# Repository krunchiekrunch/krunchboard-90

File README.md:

# krunchboard-90
A custom 75% (84+5+1) ANSI mechanical keyboard powered by a Raspberry Pi Pico with KMK

# About
This keyboard has 84 regular keys, 5 programmable macro keys, and 1 switch within the rotary encoder.

## Special Keys

Media Controls:

- Double tap F1: Previous media

- Double tap F2: Pause media

- Double tap F3: Next media

Rotary encoder:

- Turn: Volume Up/Down

- Press/Fn and turn: Brightness Up/Down

- Double press: Mute

[KLE](https://www.keyboard-layout-editor.com/##@@_a:6%3B&=Esc&_a:4%3B&=F1%0AMute&=F2%0AVOLD&=F3%0AVOLU&=F4%0APrev&=F5%0APause&=F6%0ANext&_a:6%3B&=F7&=F8&=F9&=F10&_a:4%3B&=F11%0ABRID&=F12%0ABRIU&_a:5%3B&=PrtSc%0ANmLk&=Pause%0AScrLk&=Delete%0AInsert&_a:4%3B&=Rotary%0AMute%3B&@=~%0A%60&=!%0A1&=%2F@%0A2&=%23%0A3&=$%0A4&=%25%0A5&=%5E%0A6&=%2F&%0A7&=*%0A8&=(%0A9&=)%0A0&=%2F_%0A-&=+%0A%2F=&_a:6&w:2%3B&=Backspace&=Home&_a:7%3B&=%3B&@_a:4&w:1.5%3B&=Tab&=Q&=W&=E&=R&=T&=Y&=U&=I&=O&=P&=%7B%0A%5B&=%7D%0A%5D&_w:1.5%3B&=%7C%0A%5C&_a:6%3B&=Page%20Up&_a:7%3B&=%3B&@_a:4&w:1.75%3B&=Caps%20Lock&=A&=S&=D&=F&=G&=H&=J&=K&=L&=%2F:%0A%2F%3B&=%22%0A'&_a:6&w:2.25%3B&=Enter&=Page%20Down&_a:7%3B&=%3B&@_a:6&w:2.25%3B&=Shift&_a:4%3B&=Z&=X&=C&=V&=B&=N&=M&=%3C%0A,&=%3E%0A.&=%3F%0A%2F%2F&_a:6&w:1.75%3B&=Shift&_a:7%3B&=%E2%86%91&_a:6%3B&=End&_a:7%3B&=%3B&@_a:6&w:1.25%3B&=Ctrl&_w:1.25%3B&=Win&_w:1.25%3B&=Alt&_a:7&w:6.25%3B&=&_a:6%3B&=Alt&=Fn&=Ctrl&_a:7%3B&=%E2%86%90&=%E2%86%93&=%E2%86%92&=)

# Images

| PCB                      | 3D View                         |
|--------------------------|---------------------------------|
|    |  |
|  |    | 

# BOM

| Qty | Item                                         | Notes                                     | Cost (USD)       | URL |
|-----|----------------------------------------------|-------------------------------------------|------------------|-----|
| 89  | MX-Style key switches                        | Already have                              | 9.90             | [AE](https://www.aliexpress.com/item/1005002378701948.html) |
| 89  | Kailh MX hotswap socket                      | Already have                              | 8.11             | [AE](https://www.aliexpress.com/item/1005007052649640.html) |
| 90  | 1N4148W SOD-123 Diode                        | Already have                              | 2.32             | [AE](https://www.aliexpress.com/item/1005009063199018.html) |
| 1   | EC11E Rotary encoder (With switch)           | Already have                              | 2.42             | [AE](https://www.aliexpress.com/item/1005008413622715.html) |
| 3   | MX Stabilizer (3x2u, 1x6.25u)                | Already have                              | 2.42             | [AE](https://www.aliexpress.com/item/1005007212869086.html) |
| 1   | ANSI Keycaps set                             | Already have                              | 7.00             | [AE](https://www.aliexpress.com/item/1005007321700850.html) |
| 1   | Raspbery Pi Pico (RP2040 or RP2350)          | Already have                              | 2.30             | [AE](https://www.aliexpress.com/item/1005006054409042.html) |
| 1   | USB-C Socket (SMD)                           | Already have                              | 1.00             | N/A |
| 2   | 5.1k/4.7k 0805 SMD resistor                  | Already have                              | 1.00             | N/A |
| 4   | M2 Screw (13.9mm max, I used 12mm)           | Already have                              | 1.42             | [AE](https://www.aliexpress.com/item/1005003670389142.html) |
| 4   | M2 Heatset Insert (OD3.2mm, 3mm deep)        | Already have                              | 1.73             | [AE](https://www.aliexpress.com/item/1005007640664497.html) |
| 6   | Stick-on rubber feet (Optional)              | Already have                              | 1.18             | [AE](https://www.aliexpress.com/item/1005006832476105.html) |
| 1   | PCB                                          | (Shipping/Tax included + $20 coupon)      | 15.58            | [JLCPCB](https://jlcpcb.com) |
| 1   | 3D Printed case and plate (Blueprint only)   | print-legion                              | 4.65             | N/A |
|     |                                              | Total:                                    | 56.38 [20.23]    |     |

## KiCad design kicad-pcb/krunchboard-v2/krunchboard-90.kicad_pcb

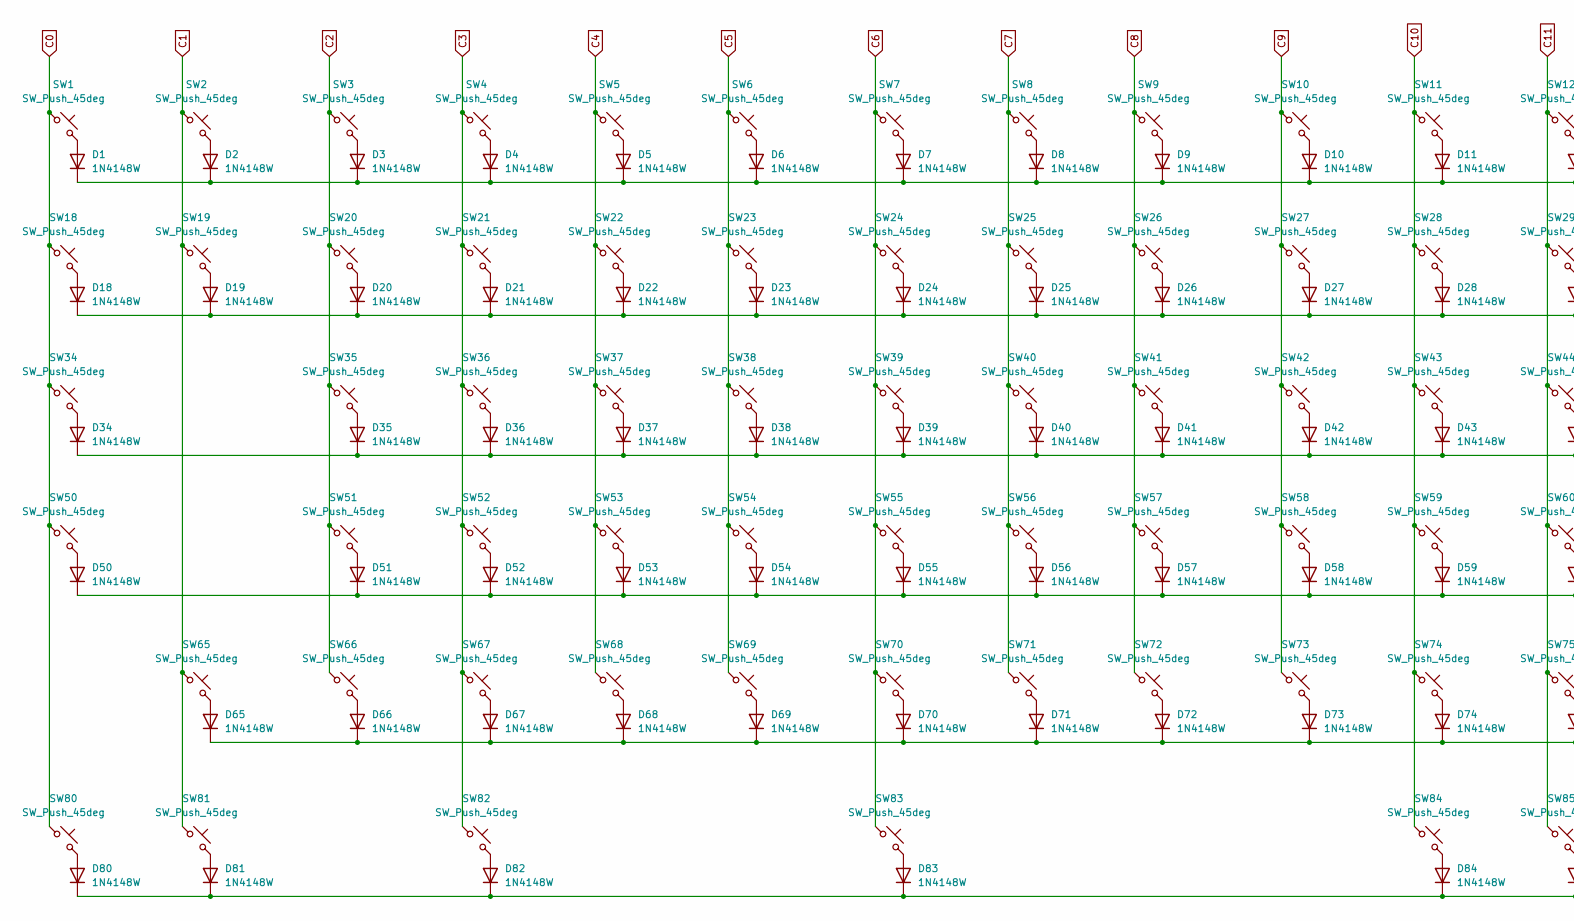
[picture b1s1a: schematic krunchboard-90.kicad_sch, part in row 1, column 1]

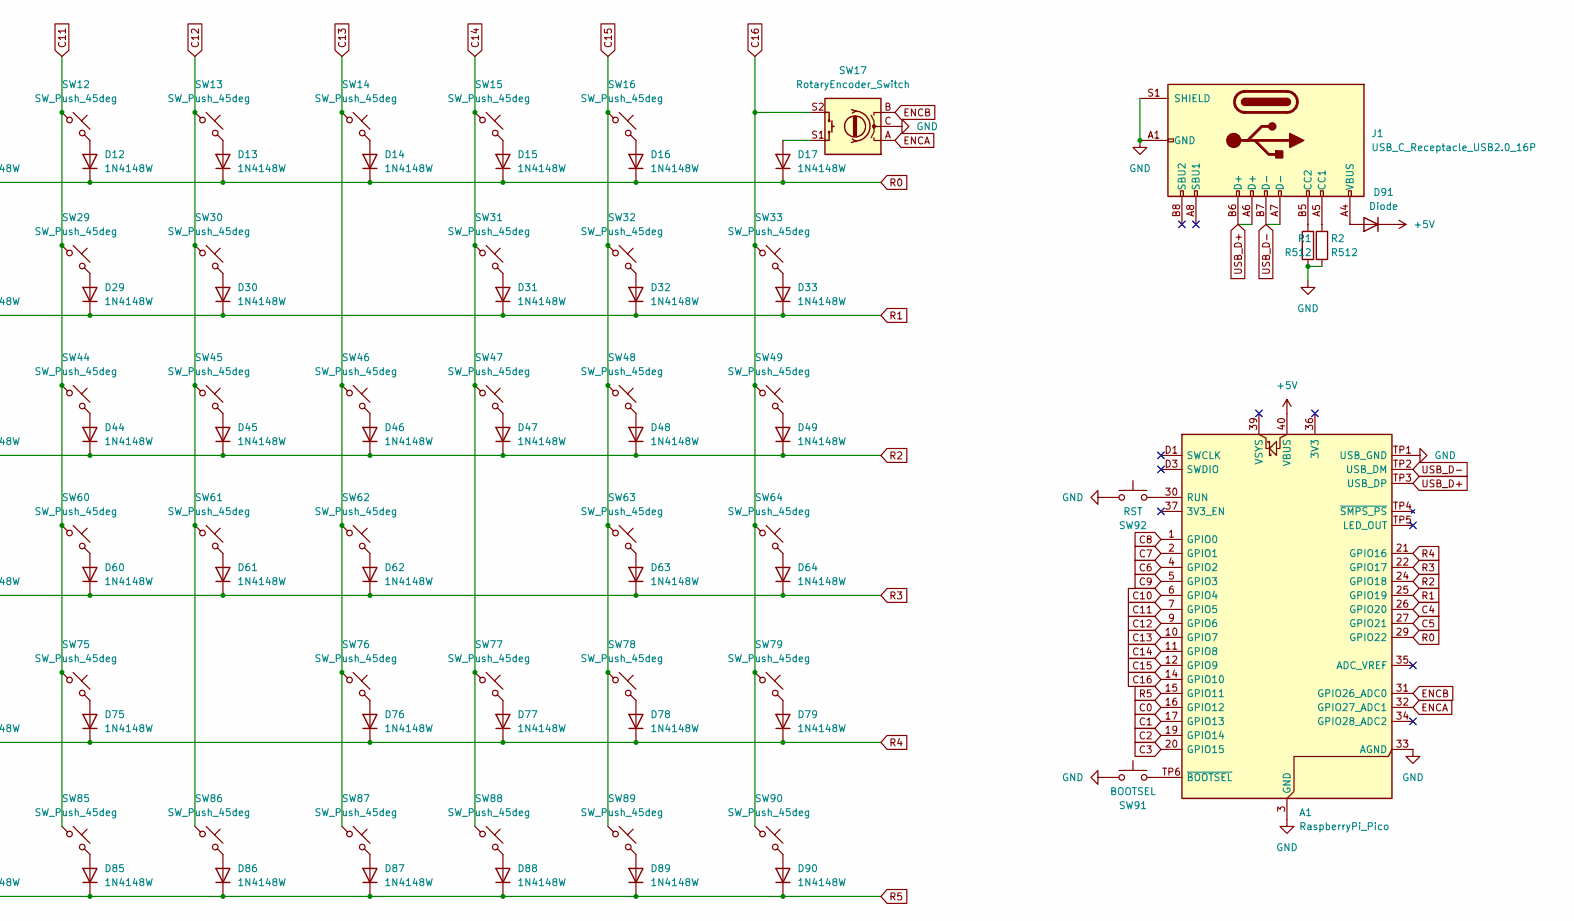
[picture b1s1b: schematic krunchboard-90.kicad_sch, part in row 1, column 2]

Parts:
A1: RaspberryPi_Pico; RaspberryPi_Pico_SMD
D1, D2, D3, D4, D5, D6, D7, D8, D9, D10, D11, D12, D13, D14, D15, D16, D17, D18, D19, D20, D21, D22, D23, D24, D25, D26, D27, D28, D29, D30, D31, D32, D33, D34, D35, D36, D37, D38, D39, D40, D41, D42, D43, D44, D45, D46, D47, D48, D49, D50, D51, D52, D53, D54, D55, D56, D57, D58, D59, D60, D61, D62, D63, D64, D65, D66, D67, D68, D69, D70, D71, D72, D73, D74, D75, D76, D77, D78, D79, D80, D81, D82, D83, D84, D85, D86, D87, D88, D89, D90: 1N4148W; D_SOD-123
D91: Diode; D_SOD-323_HandSoldering
J1: USB_C_Receptacle_USB2.0_16P; USB_C_Receptacle_HCTL_HC-TYPE-C-16P-01A
R1, R2: R512; R_0402_1005Metric_Pad0.72x0.64mm_HandSolder
SW1, SW2, SW3, SW4, SW5, SW6, SW7, SW8, SW9, SW10, SW11, SW12, SW13, SW14, SW15, SW16, SW18, SW19, SW20, SW21, SW22, SW23, SW24, SW25, SW26, SW27, SW28, SW29, SW30, SW31, SW32, SW33, SW34, SW35, SW36, SW37, SW38, SW39, SW40, SW41, SW42, SW43, SW44, SW45, SW46, SW47, SW48, SW49, SW50, SW51, SW52, SW53, SW54, SW55, SW56, SW57, SW58, SW59, SW60, SW61, SW62, SW63, SW64, SW65, SW66, SW67, SW68, SW69, SW70, SW71, SW72, SW73, SW74, SW75, SW76, SW77, SW78, SW79, SW80, SW81, SW82, SW83, SW84, SW85, SW86, SW87, SW88, SW89, SW90: SW_Push_45deg; Kailh_socket_MX_platemount_plated
SW17: RotaryEncoder_Switch; RotaryEncoder_Alps_EC11E-Switch_Vertical_H20mm
SW91: BOOTSEL; SW_SPST_TS-1088-xR025
SW92: RST; SW_SPST_TS-1088-xR025

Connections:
+5V: A1.40 (VBUS), D91.1 (K)
C0: A1.16 (GPIO12), SW1.1, SW18.1, SW34.1, SW50.1, SW80.1
C1: A1.17 (GPIO13), SW2.1, SW19.1, SW65.1, SW81.1
C2: A1.19 (GPIO14), SW3.1, SW20.1, SW35.1, SW51.1, SW66.1
C3: A1.20 (GPIO15), SW4.1, SW21.1, SW36.1, SW52.1, SW67.1, SW82.1
C4: A1.26 (GPIO20), SW5.1, SW22.1, SW37.1, SW53.1, SW68.1
C5: A1.27 (GPIO21), SW6.1, SW23.1, SW38.1, SW54.1, SW69.1
C6: A1.4 (GPIO2), SW7.1, SW24.1, SW39.1, SW55.1, SW70.1, SW83.1
C7: A1.2 (GPIO1), SW8.1, SW25.1, SW40.1, SW56.1, SW71.1
C8: A1.1 (GPIO0), SW9.1, SW26.1, SW41.1, SW57.1, SW72.1
C9: A1.5 (GPIO3), SW10.1, SW27.1, SW42.1, SW58.1, SW73.1
C10: A1.6 (GPIO4), SW11.1, SW28.1, SW43.1, SW59.1, SW74.1, SW84.1
C11: A1.7 (GPIO5), SW12.1, SW29.1, SW44.1, SW60.1, SW75.1, SW85.1
C12: A1.9 (GPIO6), SW13.1, SW30.1, SW45.1, SW61.1, SW86.1
C13: A1.10 (GPIO7), SW14.1, SW46.1, SW62.1, SW76.1, SW87.1
C14: A1.11 (GPIO8), SW15.1, SW31.1, SW47.1, SW77.1, SW88.1
C15: A1.12 (GPIO9), SW16.1, SW32.1, SW48.1, SW63.1, SW78.1, SW89.1
ENCA: A1.32 (GPIO27_ADC1), SW17.A
ENCB: A1.31 (GPIO26_ADC0), SW17.B
GND: A1.3 (GND), A1.8 (GND), A1.13 (GND), A1.18 (GND), A1.23 (GND), A1.28 (GND), A1.33 (AGND), A1.38 (GND), A1.D2 (GND), A1.TP1 (USB_GND), J1.A1 (GND), J1.A12 (GND), J1.B1 (GND), J1.B12 (GND), J1.S1 (SHIELD), R1.2, R2.2, SW17.C, SW91.1, SW92.1
unnamed: A1.30 (RUN), SW92.2
unnamed: A1.TP6 (~BOOTSEL), SW91.2
unnamed: D1.2 (A), SW1.2
unnamed: D2.2 (A), SW2.2
unnamed: D3.2 (A), SW3.2
unnamed: D4.2 (A), SW4.2
unnamed: D5.2 (A), SW5.2
unnamed: D6.2 (A), SW6.2
unnamed: D7.2 (A), SW7.2
unnamed: D8.2 (A), SW8.2
unnamed: D9.2 (A), SW9.2
unnamed: D10.2 (A), SW10.2
unnamed: D11.2 (A), SW11.2
unnamed: D12.2 (A), SW12.2
unnamed: D13.2 (A), SW13.2
unnamed: D14.2 (A), SW14.2
unnamed: D15.2 (A), SW15.2
unnamed: D16.2 (A), SW16.2
unnamed: D18.2 (A), SW18.2
unnamed: D19.2 (A), SW19.2
unnamed: D20.2 (A), SW20.2
unnamed: D21.2 (A), SW21.2
unnamed: D22.2 (A), SW22.2
unnamed: D23.2 (A), SW23.2
unnamed: D24.2 (A), SW24.2
unnamed: D25.2 (A), SW25.2
unnamed: D26.2 (A), SW26.2
unnamed: D27.2 (A), SW27.2
unnamed: D28.2 (A), SW28.2
unnamed: D29.2 (A), SW29.2
unnamed: D30.2 (A), SW30.2
unnamed: D31.2 (A), SW31.2
unnamed: D32.2 (A), SW32.2
unnamed: D33.2 (A), SW33.2
unnamed: D34.2 (A), SW34.2
unnamed: D35.2 (A), SW35.2
unnamed: D36.2 (A), SW36.2
unnamed: D37.2 (A), SW37.2
unnamed: D38.2 (A), SW38.2
unnamed: D39.2 (A), SW39.2
unnamed: D40.2 (A), SW40.2
unnamed: D41.2 (A), SW41.2
unnamed: D42.2 (A), SW42.2
unnamed: D43.2 (A), SW43.2
unnamed: D44.2 (A), SW44.2
unnamed: D45.2 (A), SW45.2
unnamed: D46.2 (A), SW46.2
unnamed: D47.2 (A), SW47.2
unnamed: D48.2 (A), SW48.2
unnamed: D49.2 (A), SW49.2
unnamed: D50.2 (A), SW50.2
unnamed: D51.2 (A), SW51.2
unnamed: D52.2 (A), SW52.2
unnamed: D53.2 (A), SW53.2
unnamed: D54.2 (A), SW54.2
unnamed: D55.2 (A), SW55.2
unnamed: D56.2 (A), SW56.2
unnamed: D57.2 (A), SW57.2
unnamed: D58.2 (A), SW58.2
unnamed: D59.2 (A), SW59.2
unnamed: D60.2 (A), SW60.2
unnamed: D61.2 (A), SW61.2
unnamed: D62.2 (A), SW62.2
unnamed: D63.2 (A), SW63.2
unnamed: D64.2 (A), SW64.2
unnamed: D65.2 (A), SW65.2
unnamed: D66.2 (A), SW66.2
unnamed: D67.2 (A), SW67.2
unnamed: D68.2 (A), SW68.2
unnamed: D69.2 (A), SW69.2
unnamed: D70.2 (A), SW70.2
unnamed: D71.2 (A), SW71.2
unnamed: D72.2 (A), SW72.2
unnamed: D73.2 (A), SW73.2
unnamed: D74.2 (A), SW74.2
unnamed: D75.2 (A), SW75.2
unnamed: D76.2 (A), SW76.2
unnamed: D77.2 (A), SW77.2
unnamed: D78.2 (A), SW78.2
unnamed: D79.2 (A), SW79.2
unnamed: D80.2 (A), SW80.2
unnamed: D81.2 (A), SW81.2
unnamed: D82.2 (A), SW82.2
unnamed: D83.2 (A), SW83.2
unnamed: D84.2 (A), SW84.2
unnamed: D85.2 (A), SW85.2
unnamed: D86.2 (A), SW86.2
unnamed: D87.2 (A), SW87.2
unnamed: D88.2 (A), SW88.2
unnamed: D89.2 (A), SW89.2
unnamed: D90.2 (A), SW90.2
unnamed: D91.2 (A), J1.A4 (VBUS), J1.A9 (VBUS), J1.B4 (VBUS), J1.B9 (VBUS)
unnamed: J1.A5 (CC1), R2.1
unnamed: J1.B5 (CC2), R1.1
R0: A1.29 (GPIO22), D1.1 (K), D2.1 (K), D3.1 (K), D4.1 (K), D5.1 (K), D6.1 (K), D7.1 (K), D8.1 (K), D9.1 (K), D10.1 (K), D11.1 (K), D12.1 (K), D13.1 (K), D14.1 (K), D15.1 (K), D16.1 (K), D17.1 (K)
R1: A1.25 (GPIO19), D18.1 (K), D19.1 (K), D20.1 (K), D21.1 (K), D22.1 (K), D23.1 (K), D24.1 (K), D25.1 (K), D26.1 (K), D27.1 (K), D28.1 (K), D29.1 (K), D30.1 (K), D31.1 (K), D32.1 (K), D33.1 (K)
R2: A1.24 (GPIO18), D34.1 (K), D35.1 (K), D36.1 (K), D37.1 (K), D38.1 (K), D39.1 (K), D40.1 (K), D41.1 (K), D42.1 (K), D43.1 (K), D44.1 (K), D45.1 (K), D46.1 (K), D47.1 (K), D48.1 (K), D49.1 (K)
R3: A1.22 (GPIO17), D50.1 (K), D51.1 (K), D52.1 (K), D53.1 (K), D54.1 (K), D55.1 (K), D56.1 (K), D57.1 (K), D58.1 (K), D59.1 (K), D60.1 (K), D61.1 (K), D62.1 (K), D63.1 (K), D64.1 (K)
R4: A1.21 (GPIO16), D65.1 (K), D66.1 (K), D67.1 (K), D68.1 (K), D69.1 (K), D70.1 (K), D71.1 (K), D72.1 (K), D73.1 (K), D74.1 (K), D75.1 (K), D76.1 (K), D77.1 (K), D78.1 (K), D79.1 (K)
R5: A1.15 (GPIO11), D80.1 (K), D81.1 (K), D82.1 (K), D83.1 (K), D84.1 (K), D85.1 (K), D86.1 (K), D87.1 (K), D88.1 (K), D89.1 (K), D90.1 (K)
USB_D+: A1.TP3 (USB_DP), J1.A6 (D+), J1.B6 (D+)
USB_D-: A1.TP2 (USB_DM), J1.A7 (D-), J1.B7 (D-)

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
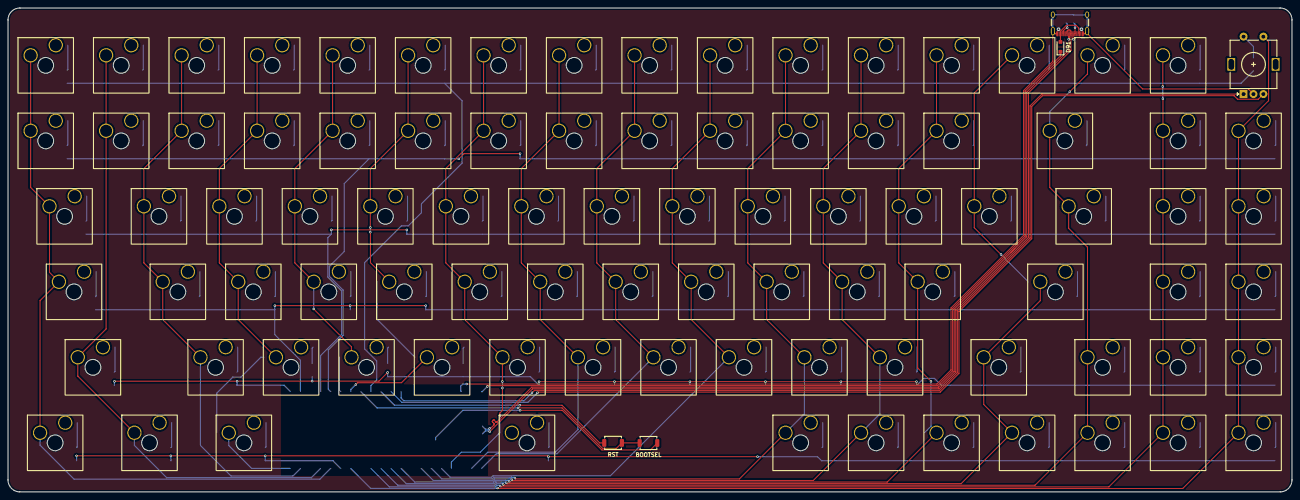
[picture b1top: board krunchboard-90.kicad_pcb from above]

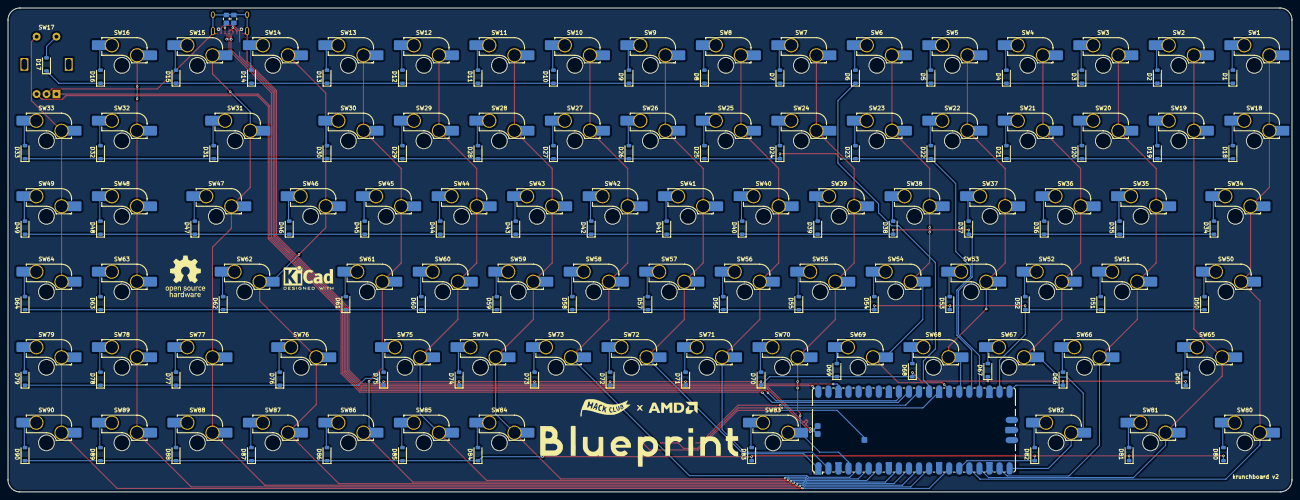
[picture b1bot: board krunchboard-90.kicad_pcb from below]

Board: 2 copper layers, 324.0 x 122.1 mm, 188 parts (94 on the bottom side), 124 nets.

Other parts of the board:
logo1: KiCad-Logo2_5mm_SilkScreen

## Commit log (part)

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2025-11-13 preview image
2025-11-13 case files, images, pcb
2025-11-14 updated readme about, formatting, bom info
2025-11-14 changed key count
2025-11-15 added coupon to bom
2025-11-15 fixed bom.csv formatting
2025-11-15 updated pcb traces, firmware
2025-11-16 code formatting
2025-11-18 updated formatting
2025-11-20 updated case,plate (added 4 extra mounting hole in center), updated pcb to prod v1
2025-11-20 updated readme images
2025-11-21 added keyboard layout editor url
2025-11-21 Integrate GPIO LED control using digitalio, added missing layer import
    Added support for controlling a GPIO LED on GP25.
2025-11-21 updated resistor package size in bom
2025-12-04 created usb_id config via boot.py
2025-12-09 added special keys, build images
2025-12-09 bom update
2025-12-09 firmware update
2025-12-09 commented out unnecessary power saving code
2025-12-09 added a screw reference chart
2025-12-09 made screw passthrough hole bigger, fixed usb-c clearance
2026-01-03 updated media controls to use tapdance instead of function, updated macros
2026-01-03 fixed pasting
2026-01-03 updated media keys docs
2026-01-19 mouse control and reset/reload
2026-01-22 updated mouse keys layout
2026-02-13 updated top of the case to hopefully fit without having to adjust heatset insert distance
2026-04-17 code documentation / renamed pcb folder
2026-04-24 updated photos
2026-04-26 made mousekeys movements twice as fast (20 > 10)
